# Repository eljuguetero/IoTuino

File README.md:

IoTuino
=======

Arduino based for Internet of Things over WiFi

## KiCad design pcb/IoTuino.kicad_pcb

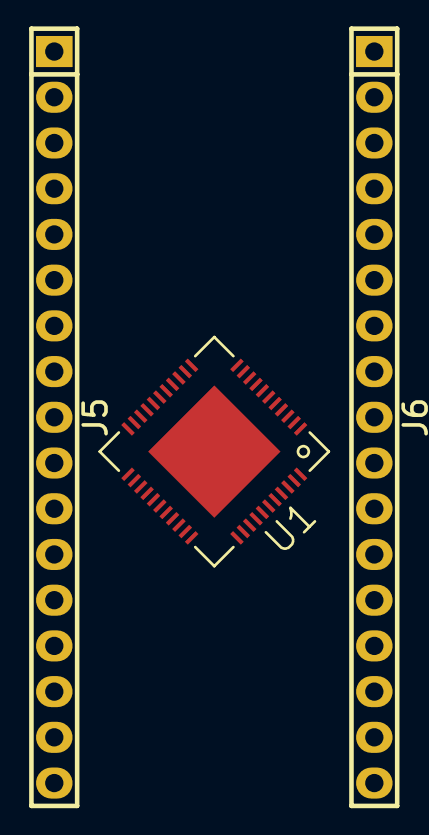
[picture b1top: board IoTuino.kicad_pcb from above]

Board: 2 copper layers, 3 parts (0 on the bottom side), 27 nets, no tracks yet.

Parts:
J5, J6: CONN_17; Pin_Header_Straight_1x17
U1: Atmega32u4-xumu; QFN-44-1EP

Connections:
/A0: J6.14, U1.36
/A1: J6.13, U1.37
/A2: J6.12, U1.38
/A3: J6.11, U1.39
/A4: J6.10, U1.40
/A5: J6.9, U1.41
/D0/RX: J5.4, U1.20
/D1/TX: J5.3, U1.21
/D2/SDA: J5.7, U1.19
/D3/SCL: J5.8, U1.18
/D4*: J5.9, U1.25
/D5*: J5.10, U1.31
/D6*: J5.11, U1.27
/IO8: J5.13, U1.28
/IO9*: J5.14, U1.29
/IO10*: J5.15, U1.30
/IO11*: J5.16, U1.12
/IO12*: J5.17, U1.26
/IO13*: J6.17, U1.32
/MISO: J6.2, U1.11
/MOSI: J5.1, U1.10
/RESET: J5.5, J6.5
/RXLED/SS: J5.2, U1.8
/SCK: J6.1, U1.9
GND: J5.6, J6.4, U1.5, U1.15, U1.23, U1.35, U1.43, U1.45
unnamed: U1.14, U1.34
unnamed: U1.24, U1.44

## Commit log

2014-08-29 just starting
